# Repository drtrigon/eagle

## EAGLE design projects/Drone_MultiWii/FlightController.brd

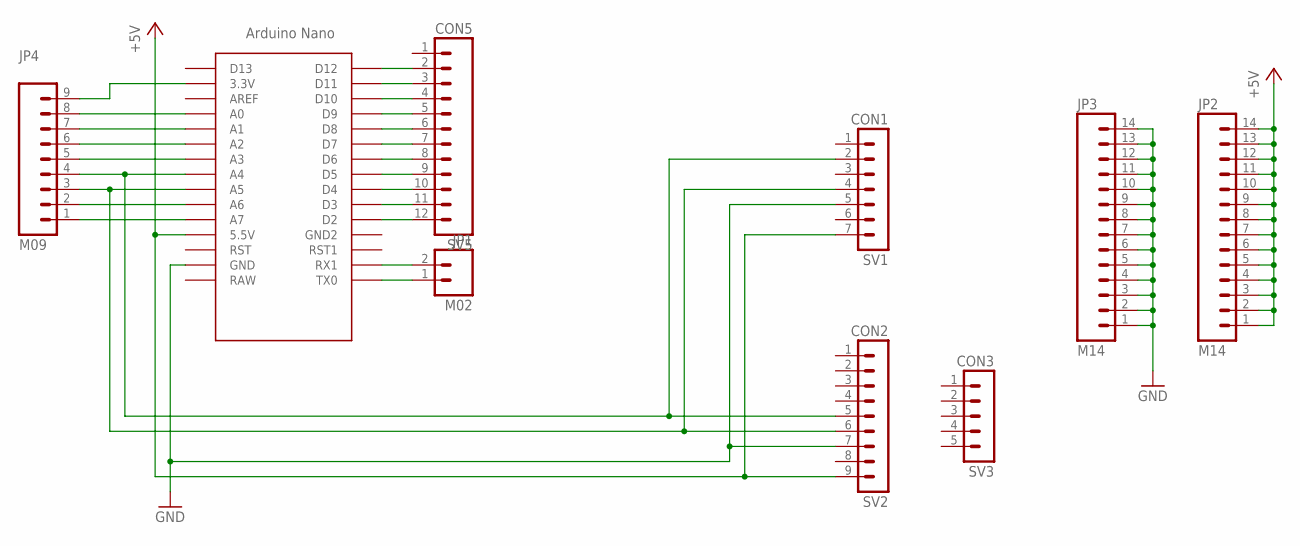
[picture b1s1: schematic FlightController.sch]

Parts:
JP1: M02; 1X02
JP2, JP3: M14; 1X14
JP4: M09; 1X09
SV1: CON1; MA07-1
SV2: CON2; MA09-1
SV3: CON3; MA05-1
SV5: CON5; 1X12
U$1: NANO

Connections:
+5V: JP2.1, JP2.2, JP2.3, JP2.4, JP2.5, JP2.6, JP2.7, JP2.8, JP2.9, JP2.10, JP2.11, JP2.12, JP2.13, JP2.14, SV1.7, SV2.9, U$1.5V (5.5V)
GND: JP3.1, JP3.2, JP3.3, JP3.4, JP3.5, JP3.6, JP3.7, JP3.8, JP3.9, JP3.10, JP3.11, JP3.12, JP3.13, JP3.14, SV1.5, SV2.7, U$1.GND
unnamed: JP4.4, SV1.2, SV2.5, U$1.A4
unnamed: JP4.3, SV1.4, SV2.6, U$1.A5
unnamed: SV5.12, U$1.D2
unnamed: SV5.11, U$1.D3
unnamed: SV5.10, U$1.D4
unnamed: SV5.9, U$1.D5
unnamed: SV5.8, U$1.D6
unnamed: SV5.7, U$1.D7
unnamed: SV5.6, U$1.D8
unnamed: SV5.5, U$1.D9
unnamed: SV5.4, U$1.D10
unnamed: SV5.3, U$1.D11
unnamed: SV5.2, U$1.D12
unnamed: JP1.2, U$1.RX1
unnamed: JP1.1, U$1.TX0
unnamed: JP4.1, U$1.A7
unnamed: JP4.2, U$1.A6
unnamed: JP4.5, U$1.A3
unnamed: JP4.6, U$1.A2
unnamed: JP4.7, U$1.A1
unnamed: JP4.8, U$1.A0
unnamed: JP4.9, U$1.3.3V

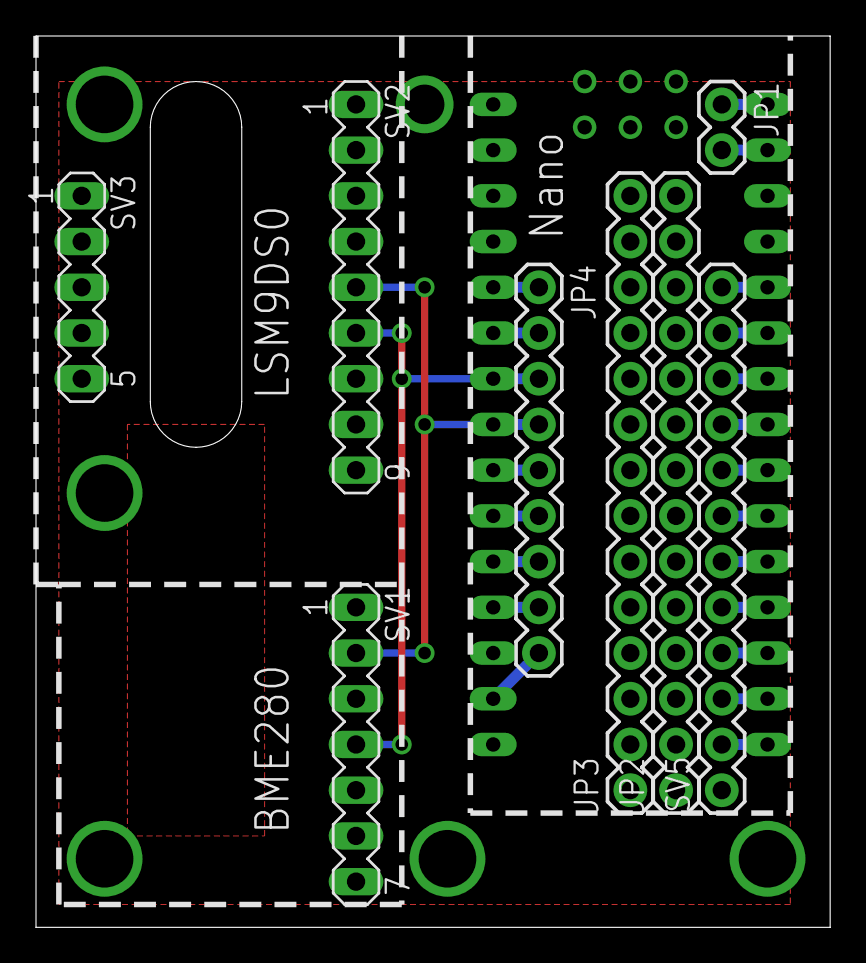
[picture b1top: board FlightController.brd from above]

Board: 2 copper layers, 44.1 x 49.5 mm, 9 parts (1 on the bottom side), 24 nets.

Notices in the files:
parts and their libraries:
SparkFun: Licensing: CC v3.0 Share-Alike You are welcome to use this library for commercial purposes.
